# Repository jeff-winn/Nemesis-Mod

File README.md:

# Nemesis Mod
It started off as me just wanting to play with an Arduino while repurposing some old .NET Gadgeteer hardware I had laying around the house. It turned into quite a bit more than that over the months that I worked on it. Hopefully the source code will help someone interested in replicating the success I had with my project with their own. Happy coding!

| Branch | Status |
| ------ | -------------|
| master |   |

## Setting up your environment
Because this project requires the use of symbolic links, you will need to use the command line to clone the repository. Visual Studio Code can do it, but it does not permit symbolic links by default.

```shell
git clone -c core.symlinks=true 
```

## Hardware Requirements
These are the boards and hardware being used by the project:
- [Adafruit Feather M4 Express](https://www.adafruit.com/product/3857) - Mainboard sketch
- [Adafruit Micro SD SPI or SDIO Card Breakout Board](https://www.adafruit.com/product/4682)
- [Tactile Button Switch (6mm square, 5mm tall)](https://www.adafruit.com/product/367)
- [Pololu Dual G2 High-Power Motor Driver 18v18 Shield for Arduino](https://www.pololu.com/product/2515)
- [Pololu G2 High-Power Motor Driver 18v17](https://www.pololu.com/product/2991)
- [Pololu 5V, 500mA Step-Down Voltage Regulator](https://www.pololu.com/product/2843)

### Optional Hardware
- [Adafruit Feather nRF52840 Express](https://www.adafruit.com/product/4062) - Bluetooth sketch
- [MaxAmps LiPo 3250 3S 11.1v Battery Pack](https://www.maxamps.com/lipo-3250-3s-11-1v-battery-pack)

## Bluetooth Support
If you wish to use the Bluetooth connectivity included with this device, please see the Wiki page.

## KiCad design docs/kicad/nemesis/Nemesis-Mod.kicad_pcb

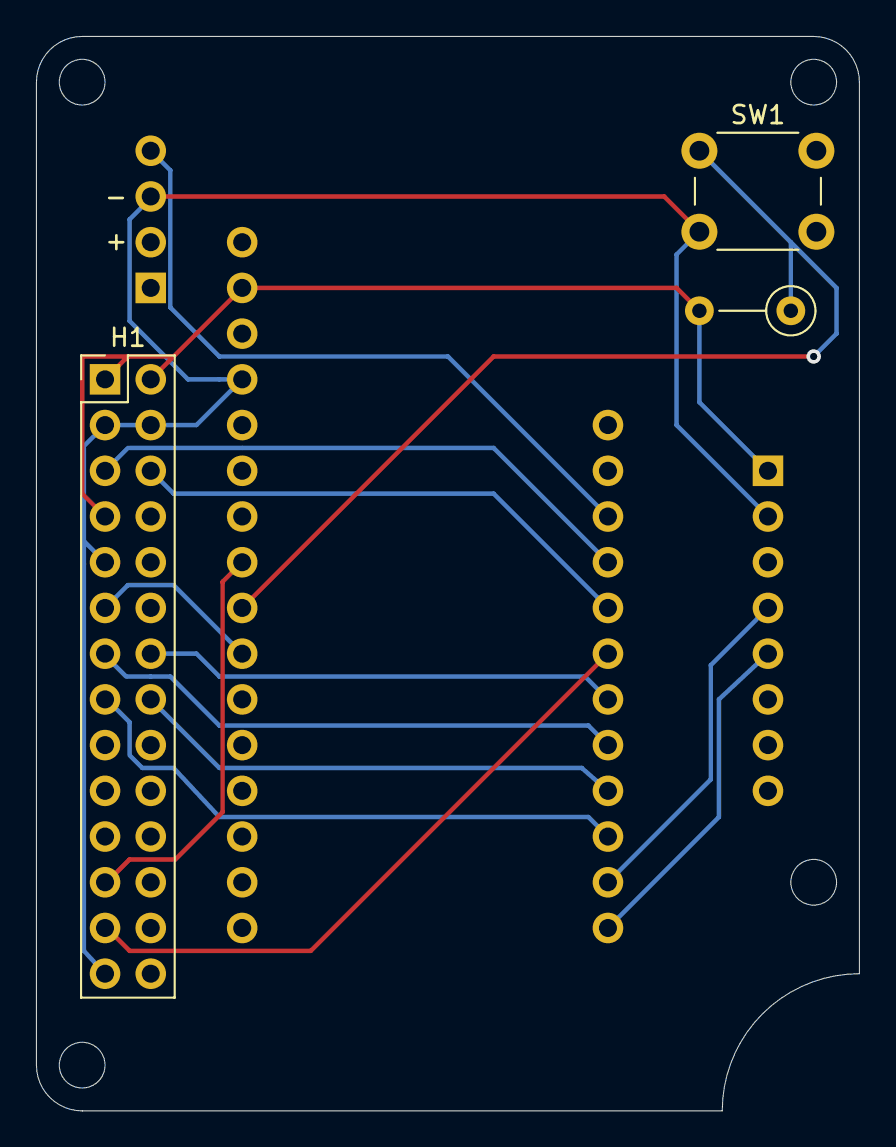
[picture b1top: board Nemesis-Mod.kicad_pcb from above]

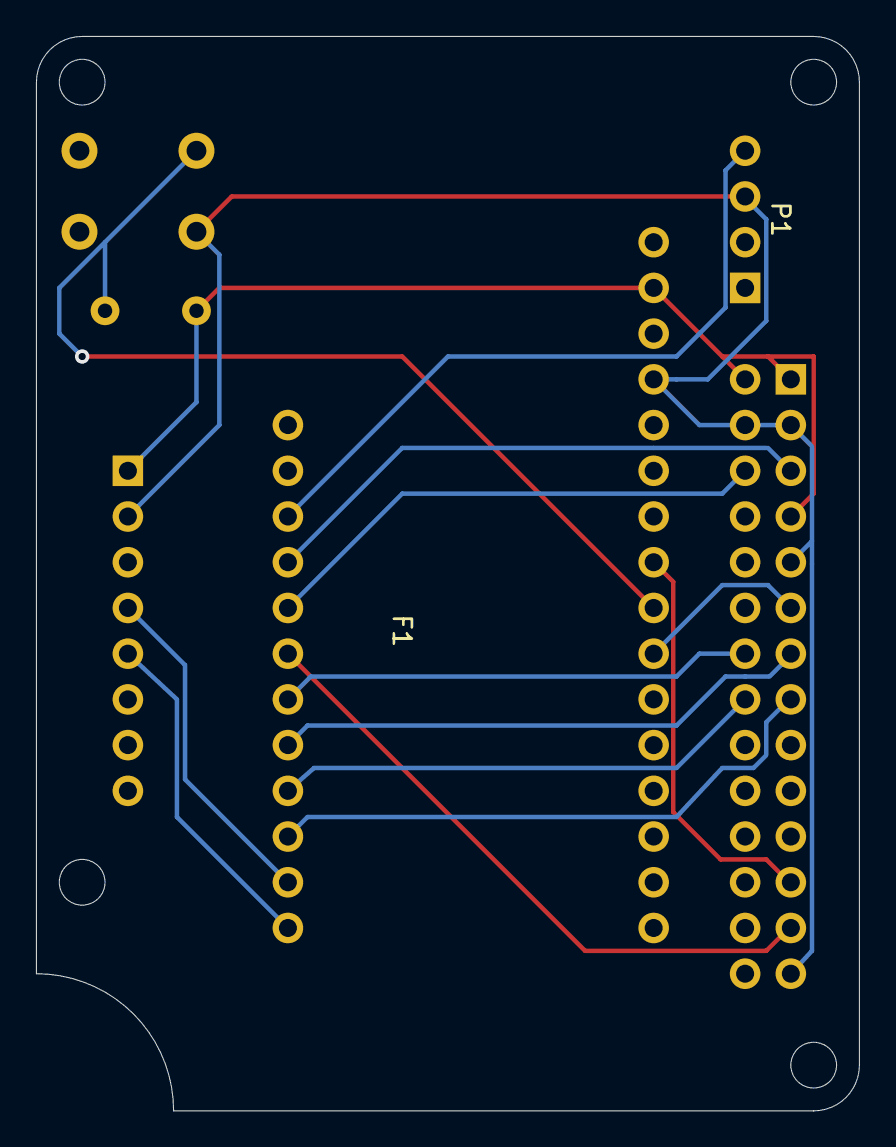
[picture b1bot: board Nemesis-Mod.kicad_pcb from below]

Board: 2 copper layers, 45.7 x 59.7 mm, 6 parts (2 on the bottom side), 15 nets.

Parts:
F1: FRAM Breakout; Adafruit_I2C_FRAM_Breakout
H1: PinHeader_2x14_P2.54mm_Vertical
MCU1: Adafruit_Feather_M4_Express
P1: Pololu_5V_Step_Down_Regulator; 5V_Step_Down_Regulator_500mA
R1: 10K; R_Axial_DIN0207_L6.3mm_D2.5mm_P5.08mm_Vertical
SW1: SW1; SW_PUSH_6mm

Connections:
+3V3: F1.1 (VCC), H1.1, H1.2, H1.7, MCU1.2 (3V), R1.2
+5V: MCU1.19 (USB), P1.4 (VOUT)
/Hopper Lock/SOFT_LOCK1: H1.11, MCU1.10 (A5)
/Mainboard/FIRE_DOWN: H1.6, MCU1.21 (12)
/Mainboard/M1PWM: H1.15, MCU1.26 (5)
/Mainboard/M1SLP: H1.13, MCU1.24 (9)
/Mainboard/M2PWM: H1.16, MCU1.25 (6)
/Mainboard/M2SLP: H1.14, MCU1.23 (10)
/Mainboard/M3PWM: H1.25, MCU1.22 (11)
/Mainboard/M3SLP: H1.23, MCU1.8 (A3)
/Mainboard/RESET_DOWN: MCU1.9 (A4), R1.1, SW1.1
/Mainboard/REV_DOWN: H1.5, MCU1.20 (13)
/Mainboard/SCL: F1.4 (SCL), MCU1.27 (SCL)
/Mainboard/SDA: F1.5 (SDA), MCU1.28 (SDA)
GND: F1.2 (GND), H1.3, H1.4, H1.9, H1.27, MCU1.4 (Gnd), P1.3 (GND), SW1.2

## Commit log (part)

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2019-11-09 Restructuring code.
2019-11-09 Restructuring callbacks.
2019-11-09 Relocating bluetooth stack.
2019-11-09 Restructuring services.
2019-11-09 Adding configuration service support.
2019-11-09 Refactoring BLE startup.
2019-11-10 Fixing conversion to float from byte array.
2019-11-11 Adding support for flywheel trim variance configuration.
2019-11-11 Adding support for modifing trim settings.
2019-11-11 Cleanup
2019-11-11 Switching constant for logging.
2019-11-11 Removing unnecessary command.
2019-11-11 Enabling security on the characteristics.
2019-11-12 Adding low power support.
2019-11-12 Correcting board version.
2019-11-12 Updating the output artifacts.
2019-11-15 Removing shutdown during development.
2019-11-17 Refactoring.
2019-11-17 Refactoring
2019-11-18 Adding support for diagnostic data on motor outputs
2019-11-18 Adding check for connected device.
2019-11-18 Fixing log text.
2019-11-25 Removing bluetooth checks.
2019-11-26 Reordering startup.
2019-11-26 Changing flywheel and belt speed enum values.
2019-11-28 Allowing changing speed to update while active.
2019-11-28 Adding hopper lock to schematic.
2019-12-01 Changing how the controllers are initialized.
2019-12-01 Renaming class to BLEController
2019-12-01 Fixing address constant name.
2019-12-06 Simplifying commands.
2019-12-06 Relocating characteristics to notification service.
2019-12-06 Fixing include guards.
2019-12-06 Removing duplicate logic.
2019-12-06 Fixing convention for private member instances.
2019-12-06 Moving hardware driver as class member.
2019-12-07 Renaming flywheel speeds.
2019-12-07 Correcting address names to match method.
2019-12-17 Updating the value names.
2019-12-17 Fixing bug with logging precision.
2019-12-17 Adding support for additional belt speed characteristics.
2019-12-17 Fixing bug with the trim adjustments not being persisted.
2019-12-17 Cleanup.
2019-12-17 Refactoring the command creation into a separate class.
2019-12-18 Changing the controllers to use the settings to prevent requiring reset to change configuraiton.
2019-12-19 Rewiring for soft hopper lock.
2019-12-19 Adding hopper soft lock.
2019-12-19 Adding Adafruit packages index.
2019-12-19 Updating flywheel default speeds to reach fps targets.
2019-12-20 Adding missing include.
2019-12-20 Fixing hopper lock initialization.
2019-12-20 Correcting schematic for VIN and GND to MCU.
2019-12-20 Refactoring changes.
2019-12-21 Adding hopper lock characteristic support.
2019-12-25 Renaming method.
2019-12-25 Fixing bug with lockout.
2019-12-30 Adding name to scan response.
2020-08-09 Adding extension recommendations.
2020-09-01 Updating README.md
2020-09-01 Updating tools path.
2020-09-01 Correcting browse path.
2020-09-04 Updating include and browse paths for 0.20.5 firmware.
2020-09-04 Updating defines.
2020-09-04 Fixing issue with the feed controller.
2020-09-05 Updating include paths.
2020-09-13 Deleting unused file.
2020-09-13 Fixing kicad file ignore.
2020-09-14 Relocating files.
2020-09-14 Updating schematic date.
2020-12-26 Fixing default value for flywheel speed.
2021-01-16 Enabling debugging support using JLink.
2021-05-14 Refactoring bluetooth firmware.
2021-05-14 Renaming folder.
2021-05-15 Relocating callbacks to bluetooth project.
2021-05-15 Fixing makefile.
2021-05-16 Updating the C++ properties file.
2021-05-16 Fixing ignore.
2021-05-16 Cleanup of unnecessary methods.
2021-05-16 Updating schematic.
2021-05-16 Updating pins to M4 equivalent.
2021-05-17 Updating pinout.
2021-05-18 Reorganizing.
2021-05-18 Updates to fix build issues.
2021-05-18 Updating build folders.
2021-05-19 Fixing include path.
2021-05-19 Updating documentation with hardware changes.
2021-05-20 Adding launch.json.
2021-11-23 Removing file from source control.
2021-11-23 Adding dependency versions.
2021-11-24 Adding CI action.
2021-11-24 Adding artifact upload.
2021-11-24 Adding release builds.
2021-11-24 Removing appveyor.yml file.
2021-11-24 Updating readme to contain new status badge.
2021-11-24 Triggering build.
2021-11-24 Removing Bluetooth support to transfer to the M4 express mainboard.
2021-11-24 Updating the board details.
2021-11-24 Updating Arduino CLI to 0.20.0
2021-11-24 Upgrading Adafruit FRAM I2C library to 2.0.0
2021-11-24 Updating read/write method signatures.
2021-11-24 Adding M4 pinout documentation.
2021-11-24 Adding debugger support.
2021-11-24 Removing mechanism to wait for usb connection.
2021-11-24 Correcting MCU1 to Feather M4.
2021-11-24 Adding launch.json config file.
2021-11-25 Removing the log entries.
2021-11-25 Removing logging (debugger now capable).
2021-11-25 Cleanup - fixing compilation warnings.
2021-11-25 Rearranging workspace.
2021-11-25 Reorganizing sketches.
2021-11-25 Updating build ocnfiguration.
2021-11-25 Updating project locations.
2021-11-25 Correcting build pipelines.
2021-11-25 Reconfiguring sketches.
2021-11-25 Relocating source files.
2021-11-25 Enabling bluetooth services and controller.
2021-11-25 Correcting artifacts uploaded.
2021-11-25 Moving BLE initialization logic out of mainboard.
2021-11-26 Relocating the callbacks into the bluetooth sketch.
2021-11-26 Adding interrupt pin.
2021-11-27 Adding interrupt support.
2021-11-27 Fixing bug.
2021-11-27 Adding transmit buffer.
2021-11-27 Relocating the configuration settings to shared folder.
2021-11-27 Adding dependency on CircularBuffer.
2021-11-27 Moving files back to the master i2c device.
2021-11-28 Removing symbolic linked folder.
2021-11-28 Removing symbolic link.
2021-11-28 Adding shared code symlinks.
2021-11-28 Relocating the BLE callback.
2021-11-28 Adding i2c command support.
2021-11-28 Fixing include.
2021-11-28 Fixing includes.
2021-11-28 Removing current notification.
2021-11-29 Updating constants.
2021-11-29 Updating NRF52 support.
2021-11-29 Adding delay to main loop.
2021-11-29 Removing unnecessary code.
2021-11-29 Reintroducing commands.
2021-11-29 Changing command to reset NRF52 device.
2021-11-29 Fixing delete for arrays.
2021-11-30 Adding commands to set transmit count from master.
2021-11-30 Enabling bluetooth remote command execution over I2C bus.
2021-11-30 Removing writes during startup.
2021-11-30 Relocating signal pin.
2021-12-01 Fixing bug with data received when not connected.
2021-12-01 Using async command to init BT hardware.
2021-12-01 Fixing bug with packet transfer.
2021-12-01 Enabling characteristic value initialization.
2021-12-01 Fixing bug with characteristic written.
2021-12-01 Updating readme with new hardware requirements.
2021-12-01 Updating hardware documentation.
2021-12-02 Relocating the shared folder.
2021-12-04 Adding custom board for consolidating pins.
2021-12-06 Fixing schematic issues after double checking before fabrication.
2021-12-06 Enabling LED on/off during both rx and tx.
2021-12-06 Enabling BT command processing while firing.
2021-12-06 Updating hardware requirements.
2021-12-06 Fixing component name.
2021-12-06 Upgrading KiCad project to v6.
2021-12-08 Updating Adafruit nRF52 board to v1.2.0
2021-12-08 Excluding KiCad cache file
2021-12-08 Reworking the schematic layout.
2021-12-08 Updating PCB to match schematic.
2021-12-08 Updating layout.
2021-12-08 Updating JLink GDB server path to use variables.
2021-12-11 Adding artifact upload to ci builds.
2021-12-11 Adding packaging section.
2021-12-11 Fixing bug with release pipeline.
2021-12-11 Adding repository.
2021-12-11 Fixing syntax.
2021-12-11 Fixing repository name.
2021-12-11 Adding zip decompression for bluetooth output.
2021-12-11 Adding board packaging.
2021-12-11 Adding python toolset.
2021-12-11 Adding environment variables for file locations.
2021-12-11 Updating pipeline.
2021-12-12 Updating path to decompress.
2021-12-12 Fixing environment variables.
2021-12-12 Adding additional comments.
2021-12-12 Disabling bluetooth sketch deployment.
2021-12-12 Updating location.
2021-12-12 Updating build results.
2021-12-12 Updating extract location.
2021-12-12 Updating output location.
2021-12-12 Updating extract location/
2021-12-12 Adding packaging for bluetooth.
2021-12-12 Relocating build updates to release workflow.
2021-12-12 Adds UF2 output support for release builds. (#94)
    Adding UF2 output support for release builds.
2021-12-12 Updating vendor documentation.
2021-12-12 Updating vendor documentation. (#95)
2021-12-13 Relocating the PIN value to the settings.
2021-12-13 Relocating the PIN value to the settings. (#100)
2021-12-13 Correcting courtyard size for M4 express.
2021-12-13 Correcting courtyard width for M4 express.
2021-12-13 Fixing some issues with the PCB layout after manfacturing completed. (#101)
    * Correcting pad sizes for custom footprints.
    * Correcting courtyard size for M4 express.
    * Correcting courtyard width for M4 express.
2021-12-13 Excluding documentation changes from triggering workflow.
2021-12-13 Adding test file.
2021-12-13 Disabling CI workflow on documentation only changes. (#102)
2021-12-14 Adding on-board documentation for power.
2021-12-14 Adding on-board documentation for power. (#103)
2021-12-15 Updating design to use SD card.
2021-12-15 Changing the config settings to use an ini file.
2021-12-16 Restructuring the examples.
2021-12-16 Relocating SPI init.
2021-12-16 Moving filename to header.
2021-12-17 Replacing INI file with JSON
2021-12-17 Restructuring config to use JSON files.
2021-12-17 Enabling support to rename blaster from config setting.
2021-12-17 Renaming feed to pusher.
2021-12-17 Renaming enum.
2021-12-17 Renaming the FeedController to PusherController.
2021-12-17 Adding SD library dependency.
2021-12-18 Adding SonarQube support to the CI workflow.
2021-12-18 Updating the scanning location.
2021-12-18 Update Makefile
2021-12-18 Adding CLI output dir flag.
2021-12-18 Updating the output directory.
2021-12-18 Updating the sources location.
2021-12-18 Correcting the scanning configuration and SCM exclusions.
2021-12-18 Adding fetch depth to fix SonarScanner warning.
2021-12-18 Adding sonar scanning to the release workflow.
2021-12-18 Adding support for SonarQube. (#105)
2021-12-18 Removing the fetch depth.
2021-12-18 Removing the fetch depth. (#106)
2021-12-18 Cleaning up some SonarQube bugs. (#107)
    * Fixing bug.
    * Fixing a couple sonar bugs.
2021-12-18 Fixing security issue with strlen.
2021-12-19 Fixing security issue.
2021-12-19 Exclude the preproc folder from scanning causing false duplication.
2021-12-19 Disabling the SCM sensor as it's not usable with Arduino CLI.
2021-12-19 Updating the preproc exclusions.
2021-12-19 Excluding any json files used by Arduino CLI from sonar scanning.
2021-12-19 Fixing security issue with strlen. (#108)
2021-12-22 Relocating the KiCad files.
2021-12-22 Removing the old images.
2021-12-22 Fixing code smell.
2021-12-22 Cleaning up code smell.
2021-12-22 FI merging master into feature/sd-card (#110)
2021-12-22 Reverting code smell.
2021-12-25 Fixing the release trigger.
2021-12-25 Fixing missing environment variables for release workflow.
2021-12-25 Fixing link
2021-12-27 Removing PRL file.
2021-12-27 Relocating the nemesis KiCad files.
2021-12-27 Updating lib locations.
2021-12-27 Correcting title block.
2021-12-27 Adding stryfe reference schematic.
2021-12-27 Removing old images.
2021-12-27 Relocating KiCad schematics.
2021-12-31 Restructuring the JSON file.
2021-12-31 Updating arduino exclusions.
2021-12-31 Updating function name.
2021-12-31 Code cleanup.
2022-01-03 Renaming the section to motor controllers.
2022-01-04 Feature/sd card (#113)
    * Updating design to use SD card.
    * Changing the config settings to use an ini file.
    * Adding example blaster ini file.
    * Update blaster.ini
    * Update blaster.ini
    * Update blaster.ini
2022-01-04 Updating documentation.
2022-01-04 Correcting documentation.
2022-01-04 Attempting to fix Sonar scanning C++ version.
    Resolves #115
2022-01-04 Code cleanup. (#116)
    * Code cleanup.
    * Code cleanup.
    * Code cleanup.
    * Code cleanup.
    * Code cleanup.
    * Code cleanup.
2024-01-07 Updating firmware.
2024-01-07 Updating build pipelines.
